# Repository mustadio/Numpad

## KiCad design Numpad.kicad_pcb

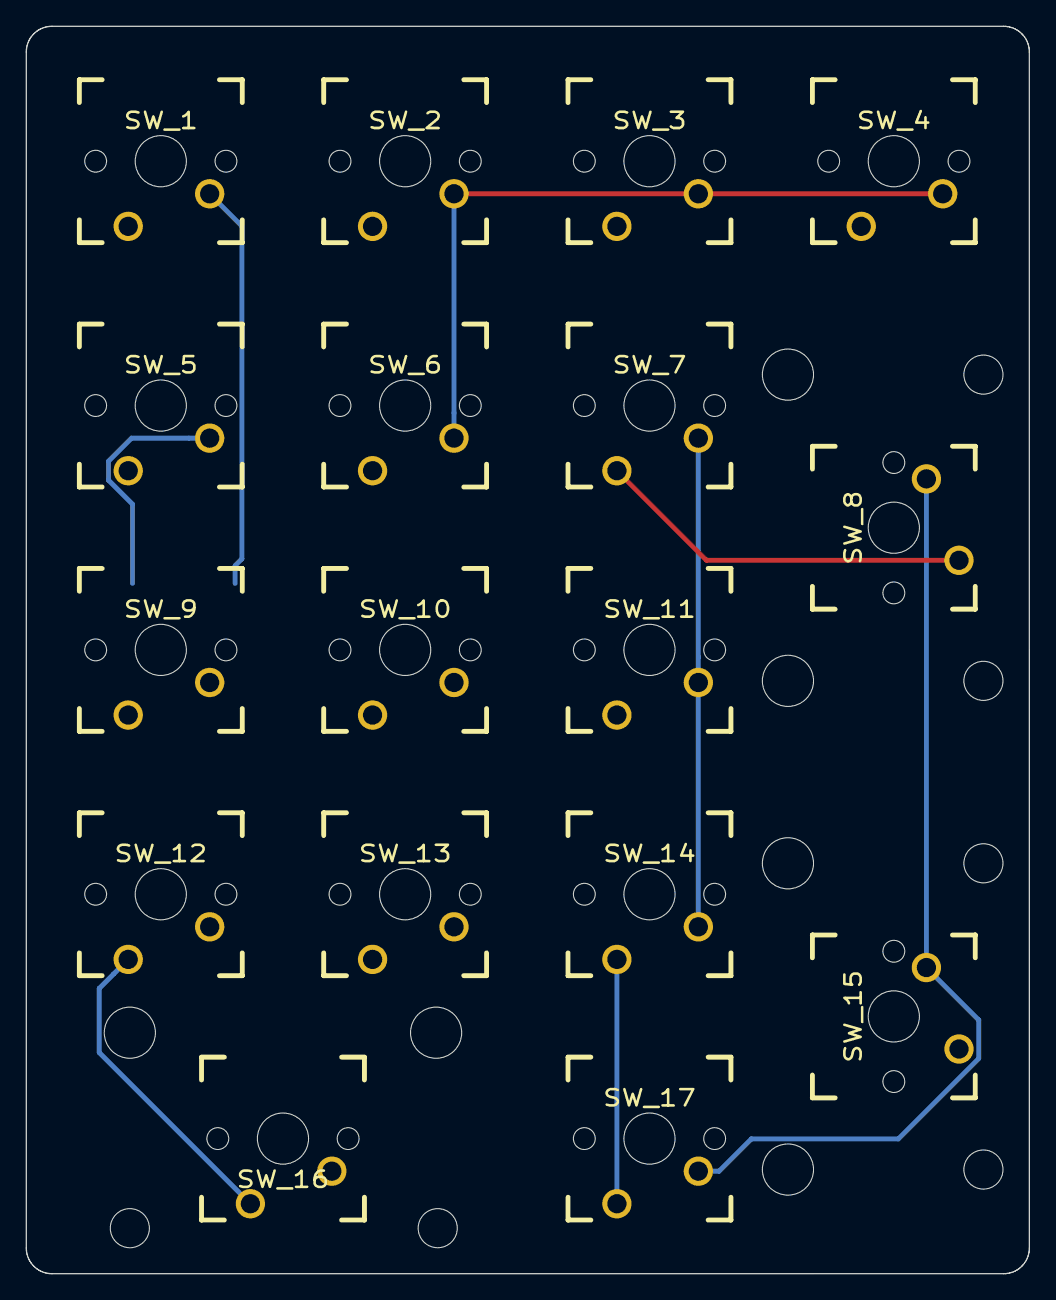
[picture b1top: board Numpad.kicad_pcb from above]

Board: 2 copper layers, 78.2 x 97.3 mm, 18 parts (1 on the bottom side), 12 nets.

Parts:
J1: K375S; TE_2-84953-7_1x27-1MP_P1.0mm_Horizontal
SW_1: Num; CHERRY_PCB_100H
SW_2: /; CHERRY_PCB_100H
SW_3: *; CHERRY_PCB_100H
SW_4: -; CHERRY_PCB_100H
SW_5: 7; CHERRY_PCB_100H
SW_6: 8; CHERRY_PCB_100H
SW_7: 9; CHERRY_PCB_100H
SW_8: +; CHERRY_PCB_200V
SW_9: 4; CHERRY_PCB_100H
SW_10: 5; CHERRY_PCB_100H
SW_11: 6; CHERRY_PCB_100H
SW_12: 1; CHERRY_PCB_100H
SW_13: 2; CHERRY_PCB_100H
SW_14: 3; CHERRY_PCB_100H
SW_15: Enter; CHERRY_PCB_200V
SW_16: 0; CHERRY_PCB_200H_RR
SW_17: .; CHERRY_PCB_100H

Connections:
unnamed: J1.1, SW_5.2, SW_8.2, SW_10.2, SW_15.2, SW_16.2, SW_17.2
unnamed: J1.2, SW_2.2, SW_3.2, SW_4.2, SW_6.2, SW_12.2
unnamed: J1.9, SW_1.2, SW_7.2, SW_11.2, SW_13.2, SW_14.2
unnamed: J1.13, SW_9.2
unnamed: J1.14, SW_1.1, SW_6.1, SW_10.1
unnamed: J1.15, SW_9.1
unnamed: J1.16, SW_15.1
unnamed: J1.17, SW_12.1, SW_16.1
unnamed: J1.19, SW_2.1, SW_7.1, SW_8.1
unnamed: J1.20, SW_4.1, SW_5.1, SW_11.1
unnamed: J1.21, SW_3.1, SW_14.1, SW_17.1
unnamed: J1.22, SW_13.1
